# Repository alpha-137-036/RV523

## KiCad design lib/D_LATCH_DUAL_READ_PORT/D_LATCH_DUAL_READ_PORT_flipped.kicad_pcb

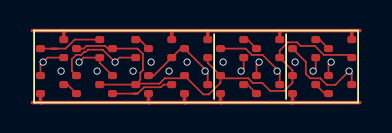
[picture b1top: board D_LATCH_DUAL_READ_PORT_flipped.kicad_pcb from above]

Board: 2 copper layers, 18 parts (0 on the bottom side), 17 nets.

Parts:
latch.NOT1.N1, latch.NOT1.N2, latch.NOT2.N1, latch.NOT3.N1, latch.NOT3.N2: NMOS; SOT523
latch.NOT1.P1, latch.NOT1.P2, latch.NOT2.P1, latch.NOT3.P1, latch.NOT3.P2: PMOS; SOT523
port1.N1, port1.N2, port2.N1, port2.N2: NMOS; SOT523
port1.P1, port1.P2, port2.P1, port2.P2: PMOS; SOT523

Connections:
CLK: latch.NOT1.N2.1 (G), latch.NOT3.P2.1 (G)
D: latch.NOT1.N1.1 (G), latch.NOT1.P1.1 (G)
GND: latch.NOT1.N1.2 (S), latch.NOT2.N1.2 (S), latch.NOT3.N1.2 (S), port1.N1.2 (S), port2.N1.2 (S)
Q: latch.NOT2.N1.3 (D), latch.NOT2.P1.3 (D), latch.NOT3.N1.1 (G), latch.NOT3.P1.1 (G)
Q1: port1.N2.3 (D), port1.P2.3 (D)
Q2: port2.N2.3 (D), port2.P2.3 (D)
VDD: latch.NOT1.P1.2 (S), latch.NOT2.P1.2 (S), latch.NOT3.P1.2 (S), port1.P1.2 (S), port2.P1.2 (S)
latch.NOT1.Y: latch.NOT1.N2.3 (D), latch.NOT1.P2.3 (D), latch.NOT2.N1.1 (G), latch.NOT2.P1.1 (G), latch.NOT3.N2.3 (D), latch.NOT3.P2.3 (D), port1.N1.1 (G), port1.P1.1 (G), port2.N1.1 (G), port2.P1.1 (G)
latch.NOT1.intN: latch.NOT1.N1.3 (D), latch.NOT1.N2.2 (S)
latch.NOT1.intP: latch.NOT1.P1.3 (D), latch.NOT1.P2.2 (S)
latch.NOT3.intN: latch.NOT3.N1.3 (D), latch.NOT3.N2.2 (S)
latch.NOT3.intP: latch.NOT3.P1.3 (D), latch.NOT3.P2.2 (S)
nCLK: latch.NOT1.P2.1 (G), latch.NOT3.N2.1 (G)
port1.intN: port1.N1.3 (D), port1.N2.2 (S)
port1.intP: port1.P1.3 (D), port1.P2.2 (S)
port2.intN: port2.N1.3 (D), port2.N2.2 (S)
port2.intP: port2.P1.3 (D), port2.P2.2 (S)

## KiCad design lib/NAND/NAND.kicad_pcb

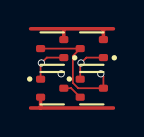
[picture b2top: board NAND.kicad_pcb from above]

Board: 2 copper layers, 4 parts (0 on the bottom side), 5 nets.

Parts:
N1, N2: SOT-523
P1, P2: SOT-523

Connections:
A: N1.1 (G), P1.1 (G)
B: N2.1 (G), P2.1 (G)
VDD: P1.2 (S), P2.2 (S)
Y: N2.3 (D), P1.3 (D), P2.3 (D)
int1: N1.3 (D), N2.2 (S)

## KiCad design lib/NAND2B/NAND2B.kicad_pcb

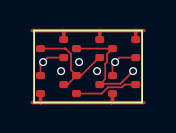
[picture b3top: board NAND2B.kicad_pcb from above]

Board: 2 copper layers, 6 parts (0 on the bottom side), 7 nets.

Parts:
N1, N2, N3: NMOS; SOT523
P1, P2, P3: PMOS; SOT523

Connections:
A: N1.3 (D), N2.1 (G), P1.3 (D), P2.1 (G)
A_N: N1.1 (G), P1.1 (G)
B: N3.1 (G), P3.1 (G)
GND: N1.2 (S), N3.2 (S)
VDD: P1.2 (S), P2.2 (S), P3.2 (S)
Y: N2.3 (D), P2.3 (D), P3.3 (D)
sndA: N2.2 (S), N3.3 (D)
